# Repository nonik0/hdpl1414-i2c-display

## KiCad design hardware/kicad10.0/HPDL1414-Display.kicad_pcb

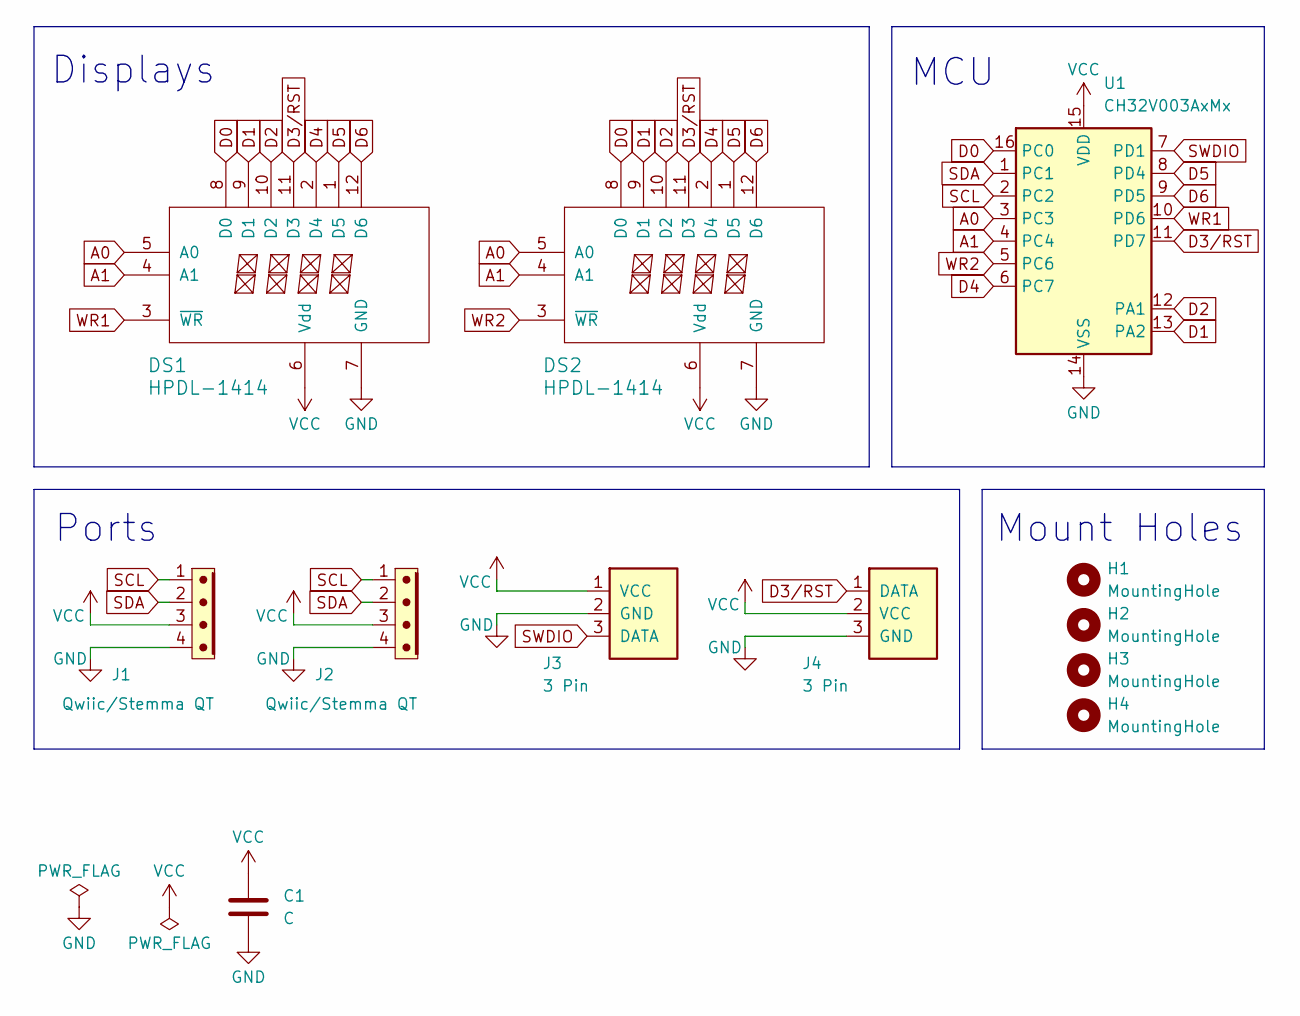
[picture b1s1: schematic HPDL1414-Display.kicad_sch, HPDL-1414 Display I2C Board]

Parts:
C1: C; C_0805_2012Metric
DS1, DS2: HPDL-1414
H1, H2, H3, H4: MountingHole; MountingHole_Custom
J1, J2: Qwiic/Stemma QT; JST_SH_4P_No Silkscreen
J3, J4: 3 Pin; Pads_1x3_2.54mm
U1: CH32V003AxMx; STC_SOP-16_3.9x9.9mm_P1.27mm

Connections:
A0: DS1.5 (A0), DS2.5 (A0), U1.3 (PC3)
A1: DS1.4 (A1), DS2.4 (A1), U1.4 (PC4)
D0: DS1.8 (D0), DS2.8 (D0), U1.16 (PC0)
D1: DS1.9 (D1), DS2.9 (D1), U1.13 (PA2)
D2: DS1.10 (D2), DS2.10 (D2), U1.12 (PA1)
D3/RST: DS1.11 (D3), DS2.11 (D3), J4.1 (DATA), U1.11 (PD7)
D4: DS1.2 (D4), DS2.2 (D4), U1.6 (PC7)
D5: DS1.1 (D5), DS2.1 (D5), U1.8 (PD4)
D6: DS1.12 (D6), DS2.12 (D6), U1.9 (PD5)
GND: C1.2, DS1.7 (GND), DS2.7 (GND), J1.4, J2.4, J3.2 (GND), J4.3 (GND), U1.14 (VSS)
SCL: J1.1, J2.1, U1.2 (PC2)
SDA: J1.2, J2.2, U1.1 (PC1)
SWDIO: J3.3 (DATA), U1.7 (PD1)
VCC: C1.1, DS1.6 (Vdd), DS2.6 (Vdd), J1.3, J2.3, J3.1 (VCC), J4.2 (VCC), U1.15 (VDD)
WR1: DS1.3 (~WR), U1.10 (PD6)
WR2: DS2.3 (~WR), U1.5 (PC6)

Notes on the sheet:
Mount Holes
MCU
Ports
Displays

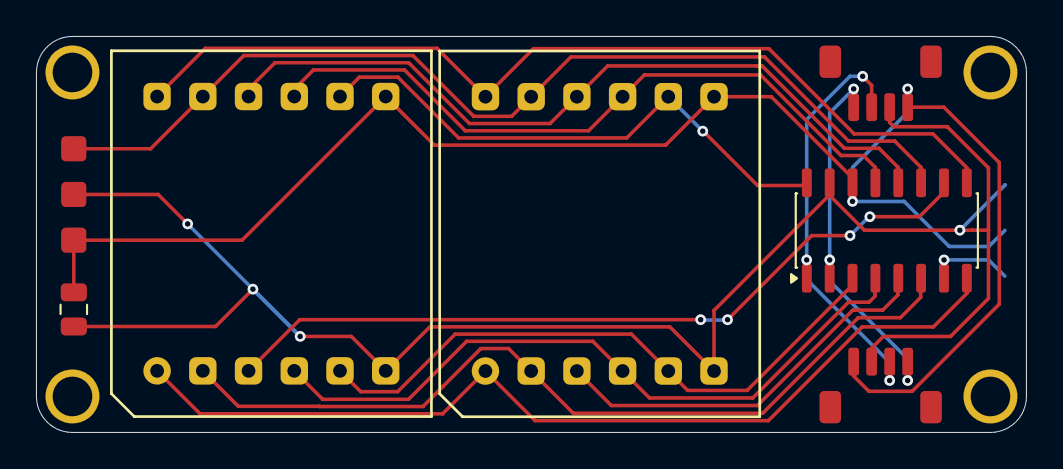
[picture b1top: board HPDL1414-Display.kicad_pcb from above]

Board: 2 copper layers, 55.0 x 22.0 mm, 12 parts (1 on the bottom side), 16 nets.

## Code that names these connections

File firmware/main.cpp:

#include <Arduino.h>
#include <Wire.h>
#include "HPDL1414.h"

#define I2C_ADDRESS 0x14
#define MAX_MESSAGE_SIZE 400
#define MIN_INTERVAL 50
#define MAX_INTERVAL 1000

// SDA=PC1, SDA=PC2
const byte dataPins[7] = {PC0, PA2, PA1, PD7, PC7, PD4, PD5}; // Segment data pins: D0 - D6
const byte addrPins[2] = {PC3, PC4};                          // Segment address pins: A0, A1
const byte wrenPins[] = {PD6, PC6};                           // Write Enable pins (left to right)

volatile bool display = true;
volatile bool scroll = true;
volatile uint16_t interval = 150;
HPDL1414 hpdl(dataPins, addrPins, wrenPins, sizeof(wrenPins));

static char messageBuffer[MAX_MESSAGE_SIZE];
static uint16_t messageLength = 0;
static uint16_t messageStart = 0;
static int16_t scrollPos = 0;
static uint32_t lastScroll = 0;

void setMessage(const char *newMessage)
{
  int displayWidth = hpdl.segments() * 4;
  int pad = displayWidth;
  int maxCopy = MAX_MESSAGE_SIZE - (2 * pad) - 1;
  int msgLen = strnlen(newMessage, maxCopy);

  int index = 0;

  // prepend spaces
  for (int i = 0; i < pad && index < MAX_MESSAGE_SIZE - 1; i++)
  {
    messageBuffer[index++] = ' ';
  }

  messageStart = index; // offset of first real character

  // copy message
  for (int i = 0; i < msgLen && index < MAX_MESSAGE_SIZE - 1; i++)
  {
    messageBuffer[index++] = newMessage[i];
  }

  // reset after clearing original message
  messageLength = index;

  // append spaces
  for (int i = 0; i < pad && index < MAX_MESSAGE_SIZE - 1; i++)
  {
    messageBuffer[index++] = ' ';
  }

  messageBuffer[index] = '\0';

  scrollPos = 0;
}

void handleOnReceive(int bytesReceived)
{
  if (bytesReceived < 2)
  {
    return;
  }

  static char buffer[MAX_MESSAGE_SIZE];
  static int bufferIndex = 0;

  uint8_t command = Wire.read();

  // setDisplay
  if (command == 0x00)
  {
    display = Wire.read();
  }
  // setMessage
  else if (command == 0x01)
  {
    // read chunk into buffer, discard extra bytes if past buffer size
    while (Wire.available())
    {
      uint8_t byte = Wire.read();
      if (bufferIndex < MAX_MESSAGE_SIZE - 1)
      {
        buffer[bufferIndex++] = byte;
      }
    }
    buffer[bufferIndex] = '\0';

    // last chunk (or buffer overflow)
    if (bufferIndex > 0 && (buffer[bufferIndex - 1] == '\n' || bufferIndex >= MAX_MESSAGE_SIZE - 1))
    {
      if (buffer[bufferIndex - 1] == '\n')
      {
        buffer[--bufferIndex] = '\0';
      }

      setMessage(buffer);
      bufferIndex = 0;
    }
  }
  // setScrollSpeed
  else if (command == 0x02)
  {
    uint8_t scrollSpeed = Wire.read();
    interval = map(constrain(scrollSpeed, 0, 100), 100, 0, MIN_INTERVAL, MAX_INTERVAL);
  }
  // setScrollMode
  else if (command == 0x03)
  {
    scroll = Wire.read();
    scrollPos = 0;
  }
  // showTempMessage
  // else if (command == 0x04) {
  // }
}

void setup()
{
  if (!hpdl.begin())
  {
    while (true)
      ;
  }

  Wire.begin(I2C_ADDRESS);
  Wire.onReceive(handleOnReceive);

  setMessage("Once upon a midnight dreary...");
}

void loop()
{
  if (millis() - lastScroll >= interval)
  {
    lastScroll = millis();
    hpdl.clear();

    if (!display)
      return;

    if (scroll)
    {
      hpdl.print(messageBuffer + scrollPos);
      scrollPos = (scrollPos + 1) % messageLength;
    }
    else
    {
      hpdl.print(messageBuffer + messageStart);
    }
  }
}

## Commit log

2026-03-23 finish basic firmware
2026-03-24 fixes
2026-03-24 kicad 10.0, drc passing
2026-03-24 cap and debug pads
2026-03-26 adjustments
2026-04-10 change i2c address
2026-04-10 increase message size
2026-04-10 faster default message
2026-05-01 add scroll mode i2c command
